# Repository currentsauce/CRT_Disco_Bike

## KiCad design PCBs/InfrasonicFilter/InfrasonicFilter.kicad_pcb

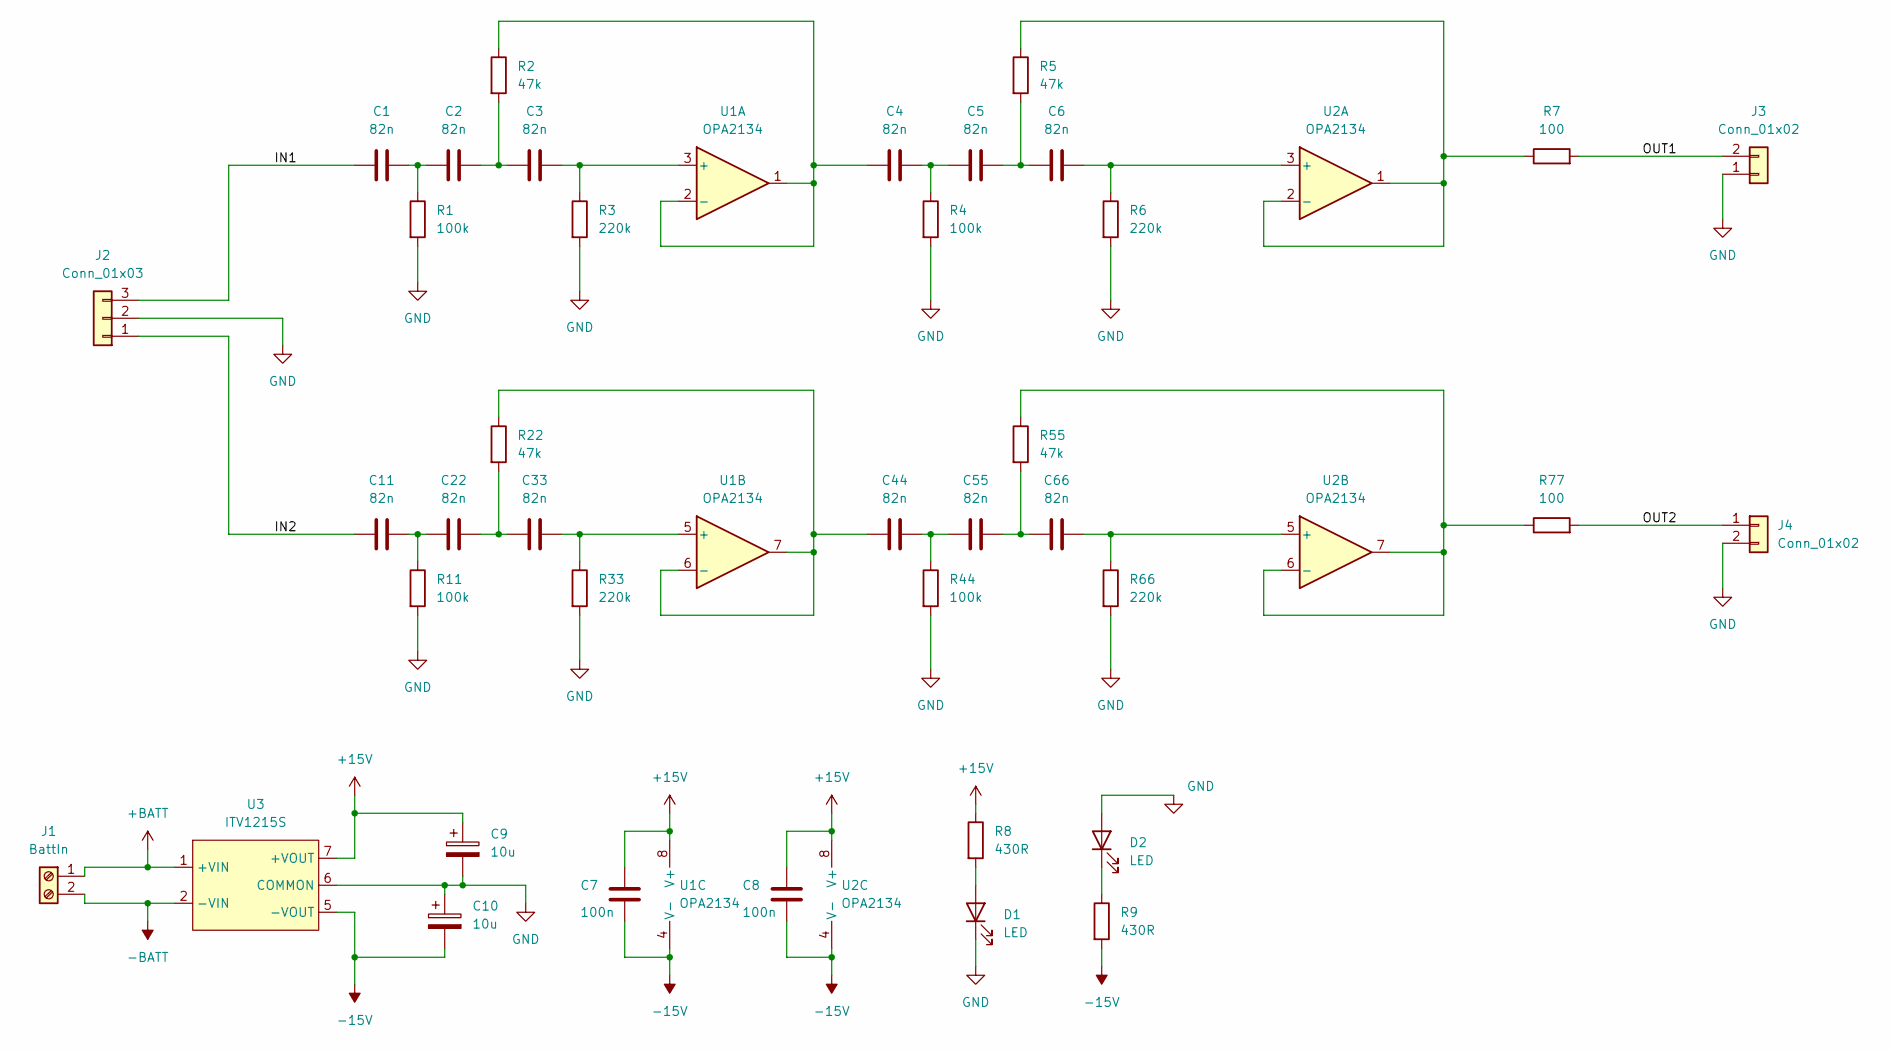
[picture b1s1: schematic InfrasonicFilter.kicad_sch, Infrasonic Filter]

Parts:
C1, C2, C3, C4, C5, C6, C11, C22, C33, C44, C55, C66: 82n; C_Disc_D4.7mm_W2.5mm_P5.00mm
C7, C8: 100n; C_Rect_L4.6mm_W3.0mm_P2.50mm_MKS02_FKP02
C9, C10: 10u; CP_Radial_D6.3mm_P2.50mm
D1, D2: LED; LED_D5.0mm
J1: BattIn; TerminalBlock_Philmore_TB132_1x02_P5.00mm_Horizontal
J2: Conn_01x03; Molex_KK-254_AE-6410-03A_1x03_P2.54mm_Vertical
J3, J4: Conn_01x02; Molex_KK-254_AE-6410-02A_1x02_P2.54mm_Vertical
R1, R4, R11, R44: 100k; R_Axial_DIN0207_L6.3mm_D2.5mm_P7.62mm_Horizontal
R2, R5, R22, R55: 47k; R_Axial_DIN0207_L6.3mm_D2.5mm_P7.62mm_Horizontal
R3, R6, R33, R66: 220k; R_Axial_DIN0207_L6.3mm_D2.5mm_P7.62mm_Horizontal
R7, R77: 100; R_Axial_DIN0207_L6.3mm_D2.5mm_P7.62mm_Horizontal
R8, R9: 430R; R_Axial_DIN0207_L6.3mm_D2.5mm_P7.62mm_Horizontal
U1, U2: OPA2134; DIP-8_W7.62mm_LongPads
U3: ITV1215S; XP_Power_ITV_Dual

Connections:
+15V: C7.1, C8.1, C9.1, R8.1, U1.8 (V+), U2.8 (V+), U3.7 (+VOUT)
+BATT: J1.1, U3.1 (+VIN)
-15V: C7.2, C8.2, C10.2, R9.2, U1.4 (V-), U2.4 (V-), U3.5 (-VOUT)
-BATT: J1.2, U3.2 (-VIN)
/IN1: C1.2, J2.3
/IN2: C11.2, J2.1
/OUT1: J3.2, R7.2
/OUT2: J4.1, R77.2
GND: C9.2, C10.1, D1.1 (K), D2.2 (A), J2.2, J3.1, J4.2, R1.2, R3.2, R4.2, R6.2, R11.2, R33.2, R44.2, R66.2, U3.6 (COMMON)
unnamed: C1.1, C2.2, R1.1
unnamed: C2.1, C3.2, R2.2
unnamed: C3.1, R3.1, U1.3 (+)
unnamed: C4.1, C5.2, R4.1
unnamed: C4.2, R2.1, U1.1, U1.2 (-)
unnamed: C5.1, C6.2, R5.2
unnamed: C6.1, R6.1, U2.3 (+)
unnamed: C11.1, C22.2, R11.1
unnamed: C22.1, C33.2, R22.2
unnamed: C33.1, R33.1, U1.5 (+)
unnamed: C44.1, C55.2, R44.1
unnamed: C44.2, R22.1, U1.6 (-), U1.7
unnamed: C55.1, C66.2, R55.2
unnamed: C66.1, R66.1, U2.5 (+)
unnamed: D1.2 (A), R8.2
unnamed: D2.1 (K), R9.1
unnamed: R5.1, R7.1, U2.1, U2.2 (-)
unnamed: R55.1, R77.1, U2.6 (-), U2.7

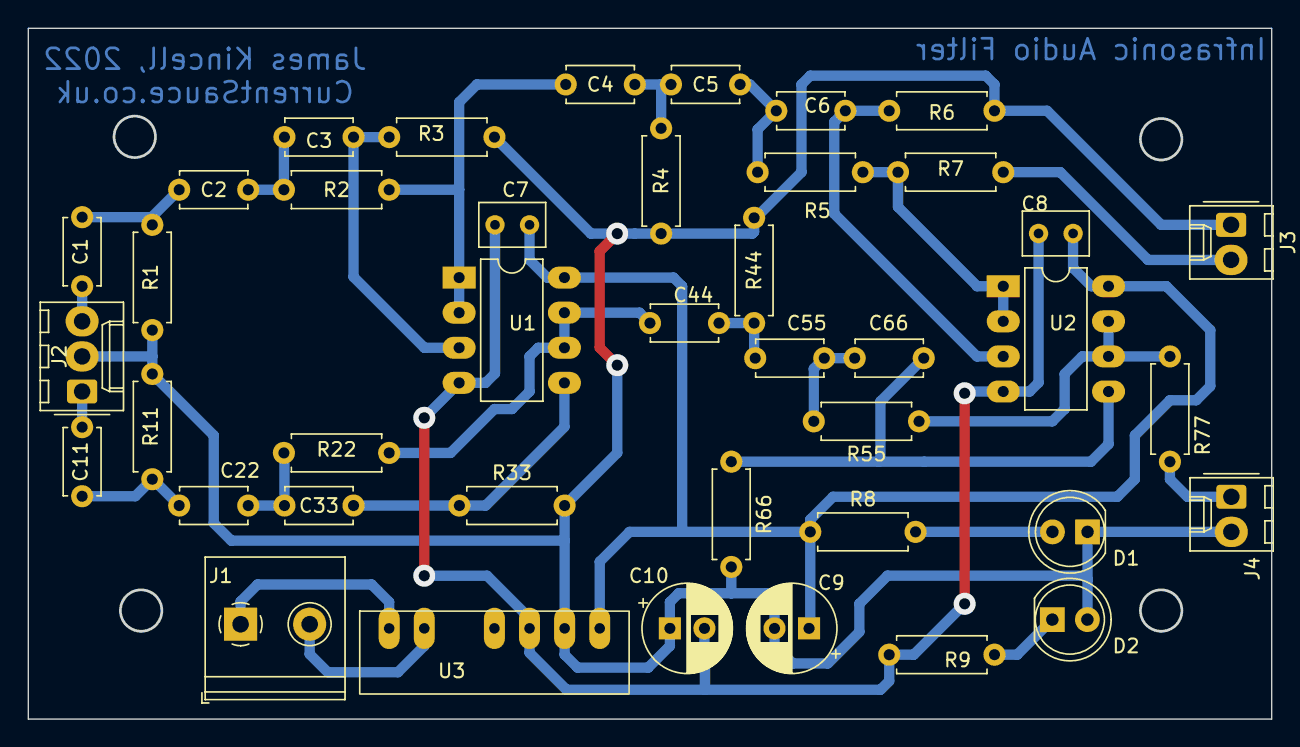
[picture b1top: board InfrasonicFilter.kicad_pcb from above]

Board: 2 copper layers, 89.9 x 49.9 mm, 41 parts (0 on the bottom side), 27 nets.

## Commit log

2022-05-30 First publish
2022-05-31 Add PCB design files and micro code
2022-05-31 Removed backups
2022-05-31 gitignore update
2022-06-07 MicroPCB Updates
2022-06-09 Bits
